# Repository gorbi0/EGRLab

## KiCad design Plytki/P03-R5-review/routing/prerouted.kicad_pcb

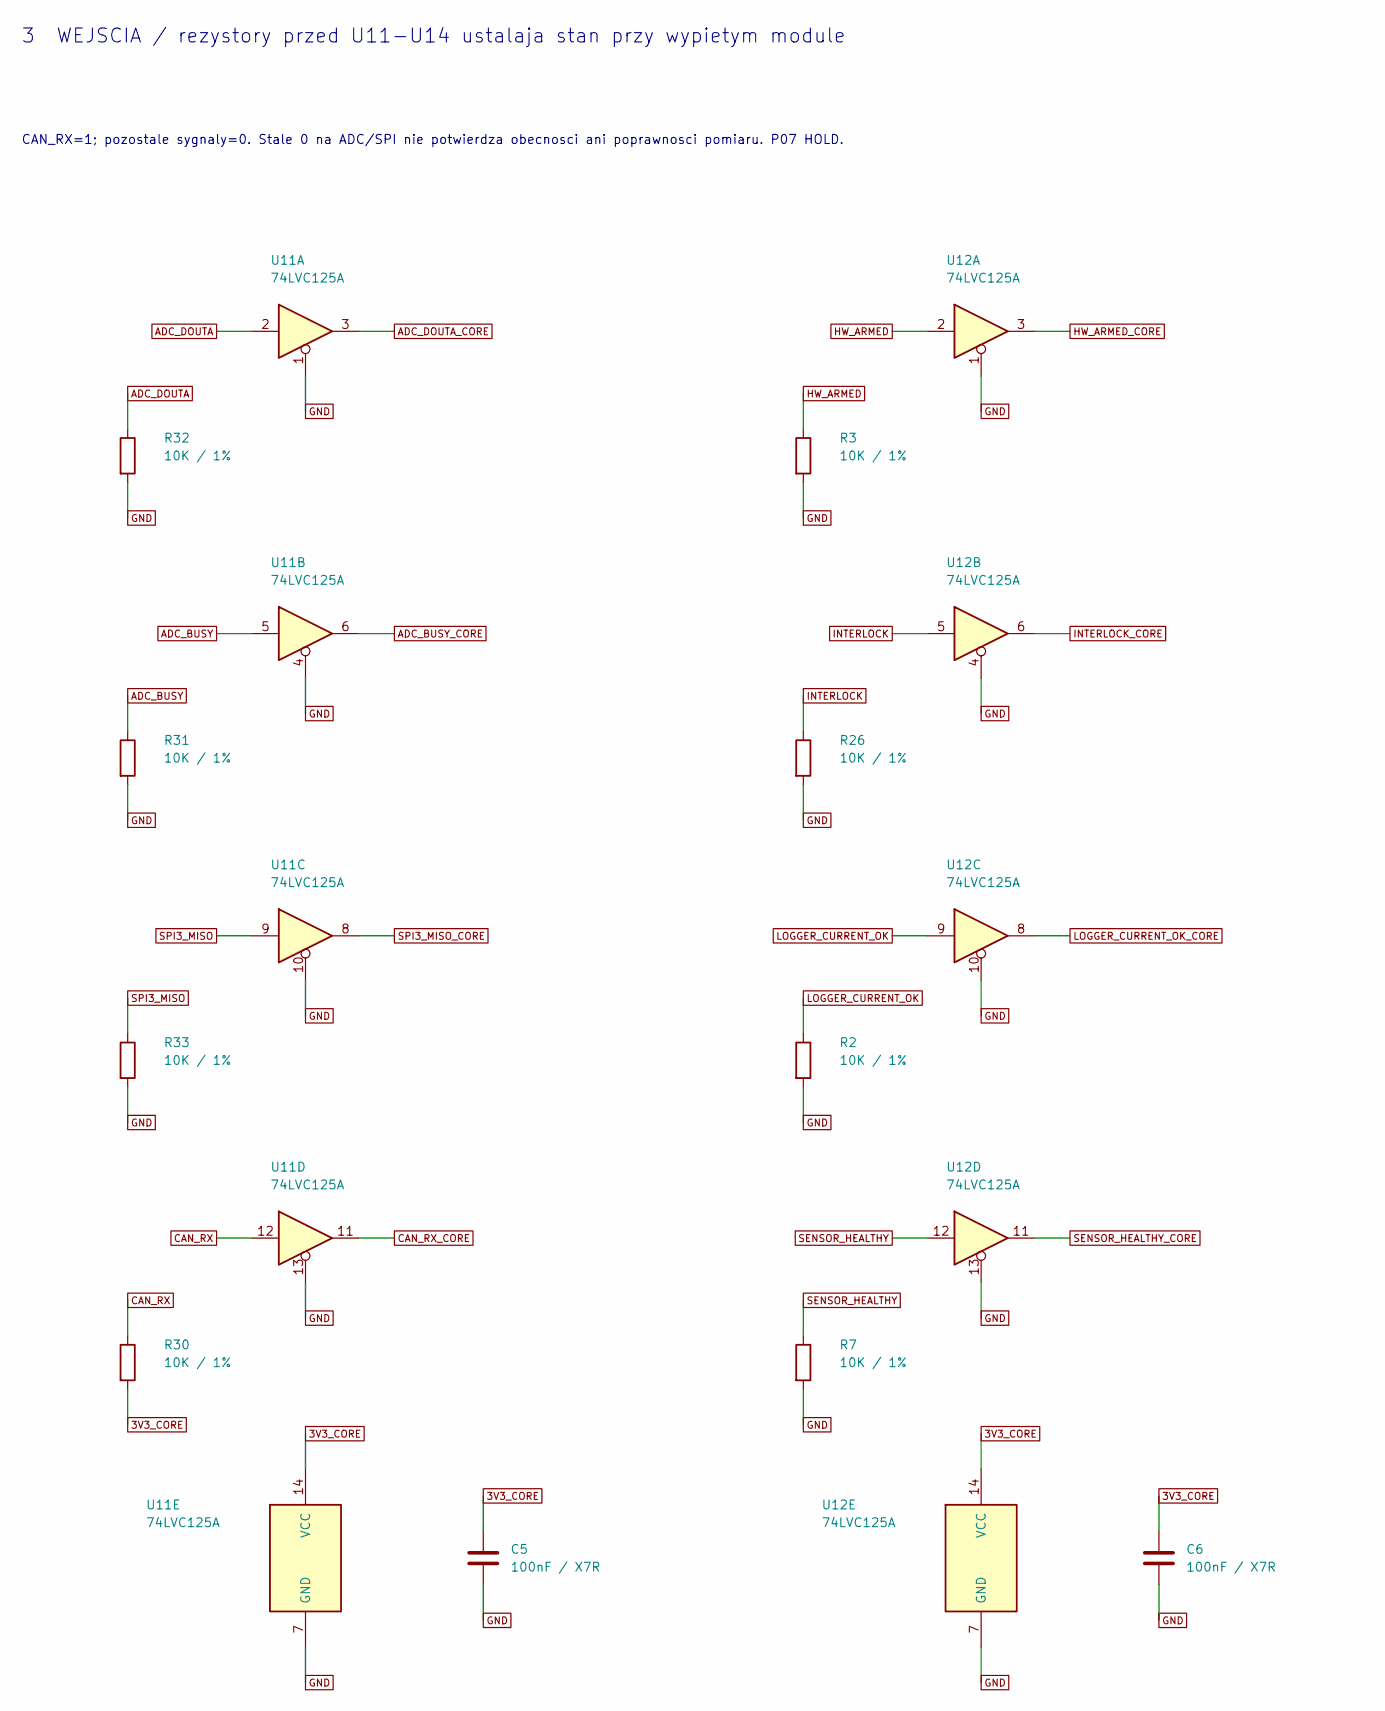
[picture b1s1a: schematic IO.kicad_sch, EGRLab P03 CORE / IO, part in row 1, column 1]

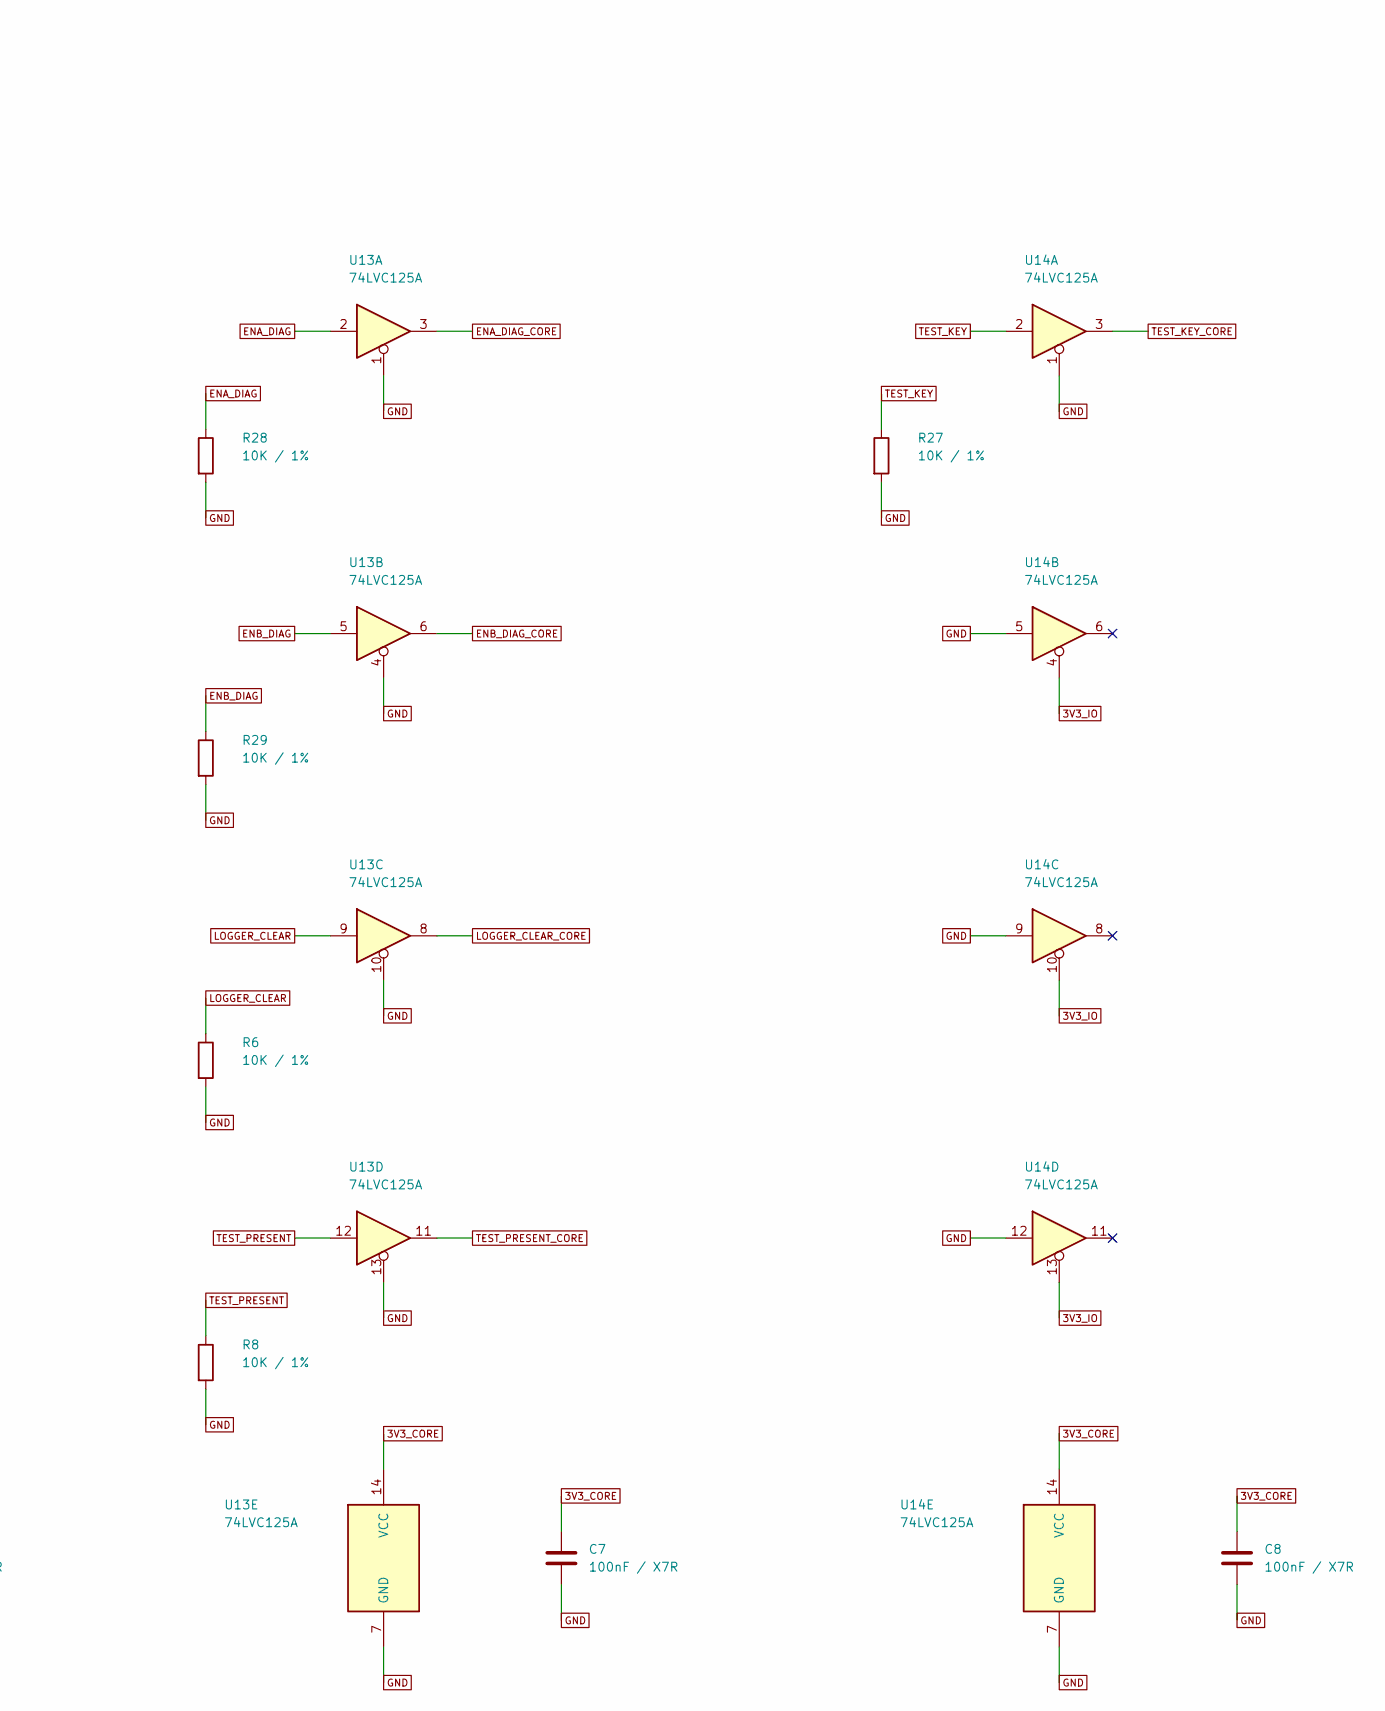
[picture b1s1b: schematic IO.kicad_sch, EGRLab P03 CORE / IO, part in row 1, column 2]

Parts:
C5, C6, C7, C8: 100nF / X7R; C_Vishay_K15_H5_P5; MPN K104K15X7RF53H5
R2, R3, R6, R7, R8, R26, R27, R28, R29, R30, R31, R32, R33: 10K / 1%; R_Axial_DIN0207_L6.3mm_D2.5mm_P10.16mm_Horizontal; MPN MF0207FTE-10K
U11, U12, U13, U14: 74LVC125A; Adapter_SO14_DIP14_W15.24_Kamami575068; MPN 74LVC125AD,118 (Nexperia) on Kamami 575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

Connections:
3V3_CORE: C5.1, C6.1, C7.1, C8.1, R30.2, U11.14 (VCC), U12.14 (VCC), U13.14 (VCC), U14.14 (VCC); also elsewhere on the board
3V3_IO: U14.4, U14.10, U14.13; also elsewhere on the board
ADC_BUSY: R31.1, U11.5; also elsewhere on the board
ADC_BUSY_CORE: U11.6; also elsewhere on the board
ADC_DOUTA: R32.1, U11.2; also elsewhere on the board
ADC_DOUTA_CORE: U11.3; also elsewhere on the board
CAN_RX: R30.1, U11.12; also elsewhere on the board
CAN_RX_CORE: U11.11; also elsewhere on the board
ENA_DIAG: R28.1, U13.2; also elsewhere on the board
ENA_DIAG_CORE: U13.3; also elsewhere on the board
ENB_DIAG: R29.1, U13.5; also elsewhere on the board
ENB_DIAG_CORE: U13.6; also elsewhere on the board
GND: C5.2, C6.2, C7.2, C8.2, R2.2, R3.2, R6.2, R7.2, R8.2, R26.2, R27.2, R28.2, R29.2, R31.2, R32.2, R33.2, U11.1, U11.4, U11.7 (GND), U11.10, U11.13, U12.1, U12.4, U12.7 (GND), U12.10, U12.13, U13.1, U13.4, U13.7 (GND), U13.10, U13.13, U14.1, U14.5, U14.7 (GND), U14.9, U14.12; also elsewhere on the board
HW_ARMED: R3.1, U12.2; also elsewhere on the board
HW_ARMED_CORE: U12.3; also elsewhere on the board
INTERLOCK: R26.1, U12.5; also elsewhere on the board
INTERLOCK_CORE: U12.6; also elsewhere on the board
LOGGER_CLEAR: R6.1, U13.9; also elsewhere on the board
LOGGER_CLEAR_CORE: U13.8; also elsewhere on the board
LOGGER_CURRENT_OK: R2.1, U12.9; also elsewhere on the board
LOGGER_CURRENT_OK_CORE: U12.8; also elsewhere on the board
SENSOR_HEALTHY: R7.1, U12.12; also elsewhere on the board
SENSOR_HEALTHY_CORE: U12.11; also elsewhere on the board
SPI3_MISO: R33.1, U11.9; also elsewhere on the board
SPI3_MISO_CORE: U11.8; also elsewhere on the board
TEST_KEY: R27.1, U14.2; also elsewhere on the board
TEST_KEY_CORE: U14.3; also elsewhere on the board
TEST_PRESENT: R8.1, U13.12; also elsewhere on the board
TEST_PRESENT_CORE: U13.11; also elsewhere on the board

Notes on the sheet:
3 WEJSCIA / rezystory przed U11-U14 ustalaja stan przy wypietym module
CAN_RX=1; pozostale sygnaly=0. Stale 0 na ADC/SPI nie potwierdza obecnosci ani poprawnosci pomiaru. P07 HOLD.

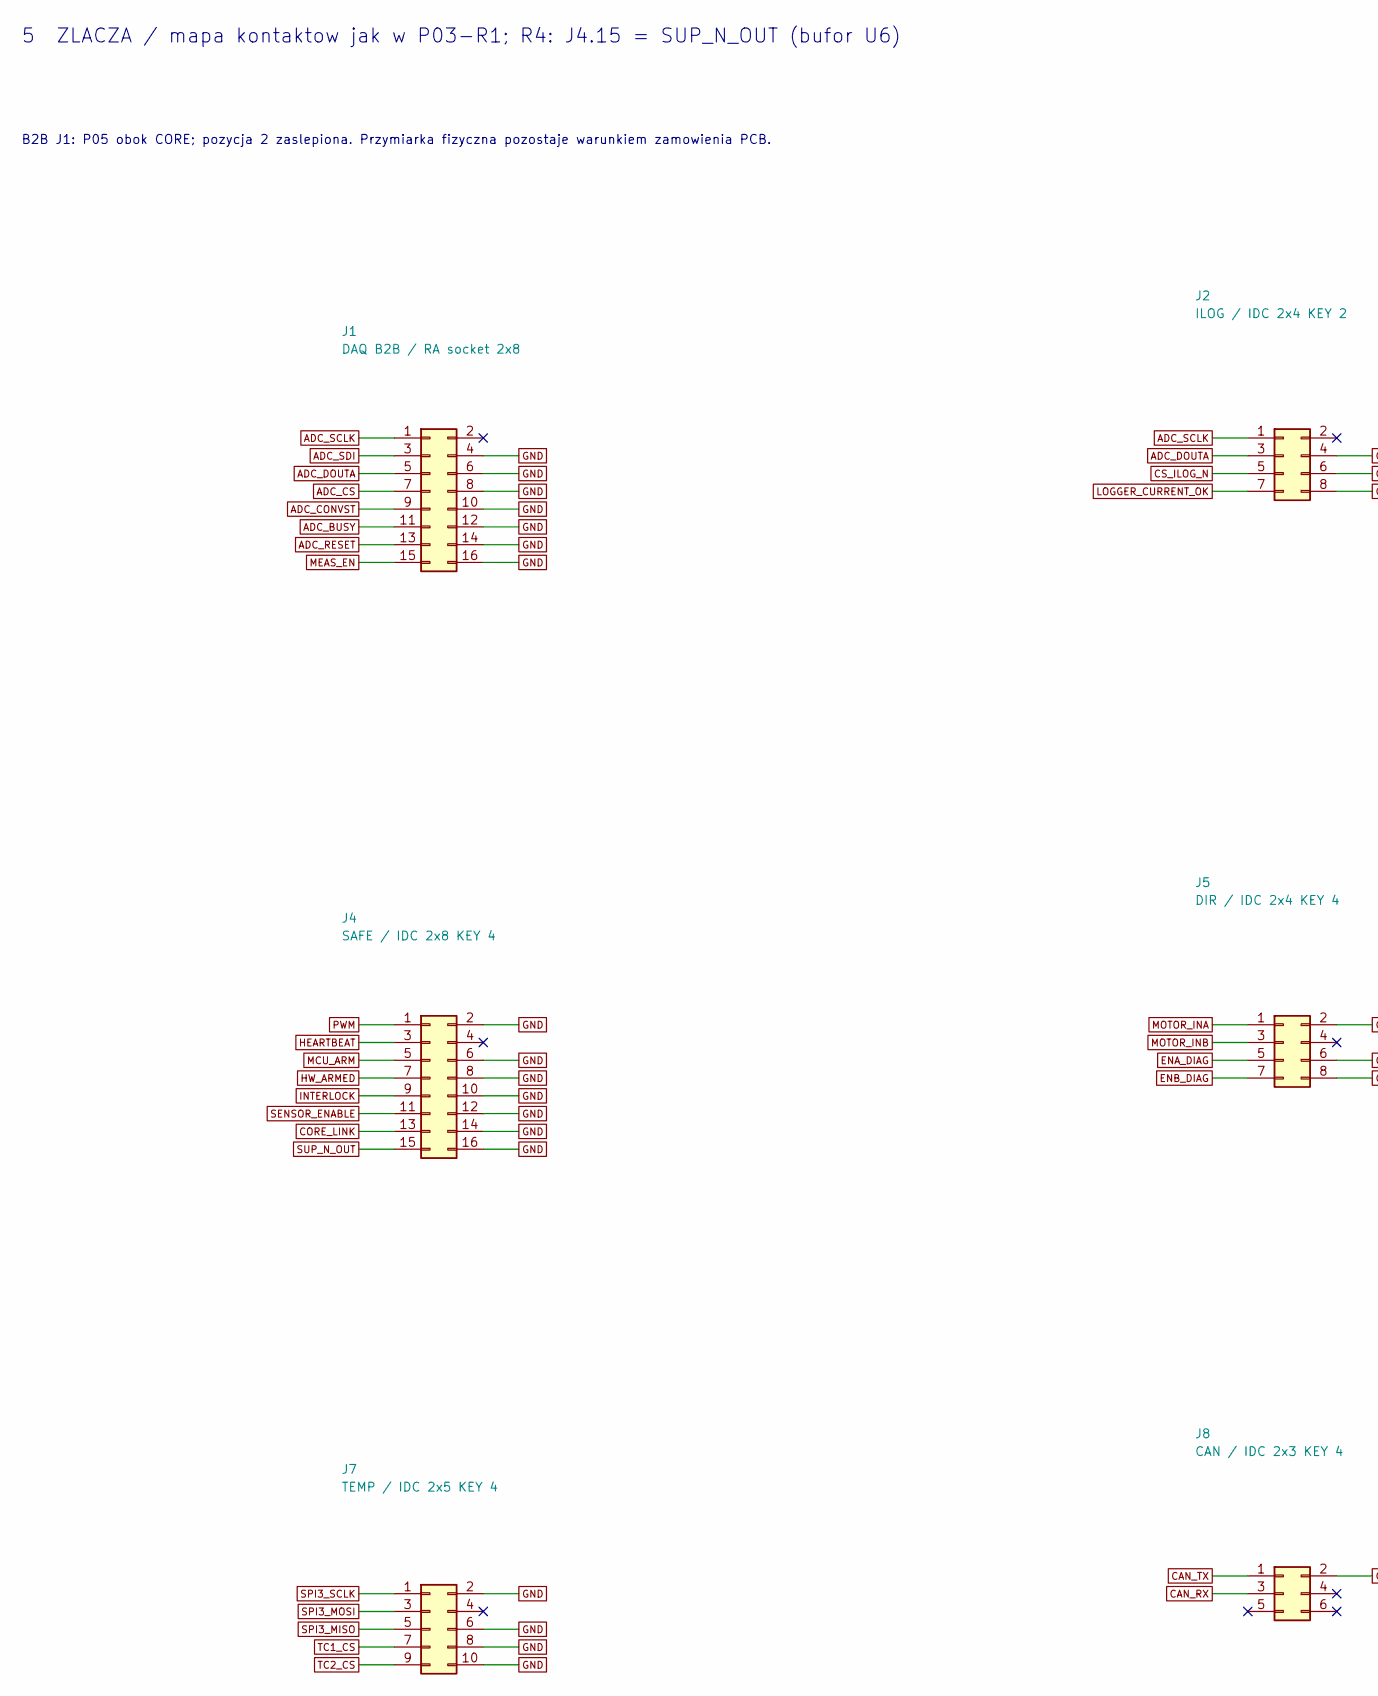
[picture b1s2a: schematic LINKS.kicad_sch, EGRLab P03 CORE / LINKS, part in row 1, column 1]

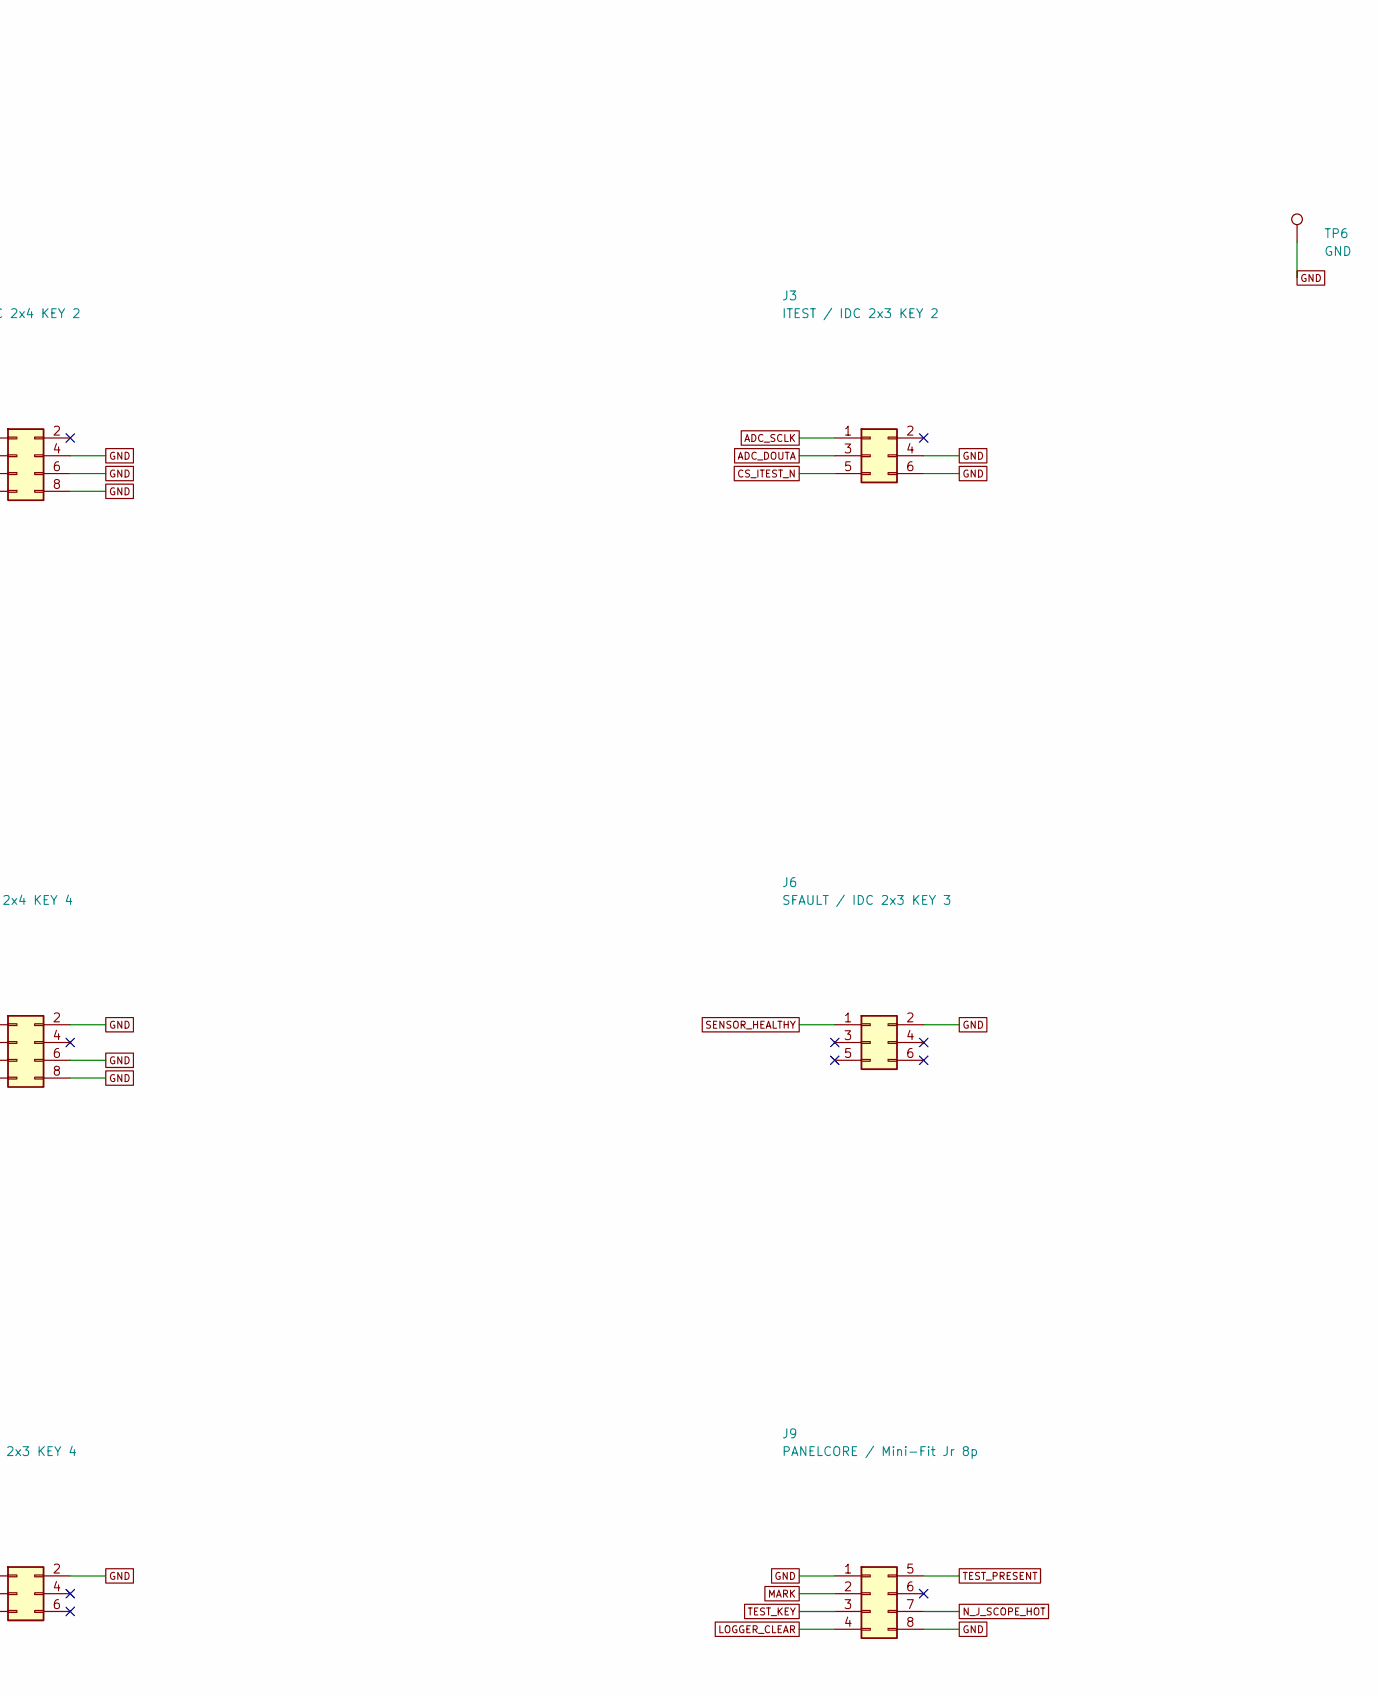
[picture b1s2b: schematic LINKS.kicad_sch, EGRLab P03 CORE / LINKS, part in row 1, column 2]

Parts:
J1: DAQ B2B / RA socket 2x8; PinSocket_2x08_P2.54mm_Horizontal; MPN Samtec SSW-108-02-G-D-RA (right-angle 2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
J2: ILOG / IDC 2x4 KEY 2; IDC-Header_2x04_P2.54mm_Vertical; MPN IDC box header 2x4, 2.54 mm, Au
J3: ITEST / IDC 2x3 KEY 2; IDC-Header_2x03_P2.54mm_Vertical; MPN IDC box header 2x3, 2.54 mm, Au
J4: SAFE / IDC 2x8 KEY 4; IDC-Header_2x08_P2.54mm_Vertical; MPN IDC box header 2x8, 2.54 mm, Au
J5: DIR / IDC 2x4 KEY 4; IDC-Header_2x04_P2.54mm_Vertical; MPN IDC box header 2x4, 2.54 mm, Au
J6: SFAULT / IDC 2x3 KEY 3; IDC-Header_2x03_P2.54mm_Vertical; MPN IDC box header 2x3, 2.54 mm, Au
J7: TEMP / IDC 2x5 KEY 4; IDC-Header_2x05_P2.54mm_Vertical; MPN IDC box header 2x5, 2.54 mm, Au
J8: CAN / IDC 2x3 KEY 4; IDC-Header_2x03_P2.54mm_Vertical; MPN IDC box header 2x3, 2.54 mm, Au
J9: PANELCORE / Mini-Fit Jr 8p; Molex_Mini-Fit_Jr_5566-08A_2x04_P4.20mm_Vertical; MPN Molex Mini-Fit Jr 5566-08A vertical, Au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
TP6: GND; TestPad_1; MPN PCB test pad

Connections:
ADC_BUSY: J1.11; also elsewhere on the board
ADC_CONVST: J1.9; also elsewhere on the board
ADC_CS: J1.7; also elsewhere on the board
ADC_DOUTA: J1.5, J2.3, J3.3; also elsewhere on the board
ADC_RESET: J1.13; also elsewhere on the board
ADC_SCLK: J1.1, J2.1, J3.1; also elsewhere on the board
ADC_SDI: J1.3; also elsewhere on the board
CAN_RX: J8.3; also elsewhere on the board
CAN_TX: J8.1; also elsewhere on the board
CORE_LINK: J4.13; also elsewhere on the board
CS_ILOG_N: J2.5; also elsewhere on the board
CS_ITEST_N: J3.5; also elsewhere on the board
ENA_DIAG: J5.5; also elsewhere on the board
ENB_DIAG: J5.7; also elsewhere on the board
GND: J1.4, J1.6, J1.8, J1.10, J1.12, J1.14, J1.16, J2.4, J2.6, J2.8, J3.4, J3.6, J4.2, J4.6, J4.8, J4.10, J4.12, J4.14, J4.16, J5.2, J5.6, J5.8, J6.2, J7.2, J7.6, J7.8, J7.10, J8.2, J9.1, J9.8, TP6.1; also elsewhere on the board
HEARTBEAT: J4.3; also elsewhere on the board
HW_ARMED: J4.7; also elsewhere on the board
INTERLOCK: J4.9; also elsewhere on the board
LOGGER_CLEAR: J9.4; also elsewhere on the board
LOGGER_CURRENT_OK: J2.7; also elsewhere on the board
MARK: J9.2; also elsewhere on the board
MCU_ARM: J4.5; also elsewhere on the board
MEAS_EN: J1.15; also elsewhere on the board
MOTOR_INA: J5.1; also elsewhere on the board
MOTOR_INB: J5.3; also elsewhere on the board
N_J_SCOPE_HOT: J9.7; also elsewhere on the board
PWM: J4.1; also elsewhere on the board
SENSOR_ENABLE: J4.11; also elsewhere on the board
SENSOR_HEALTHY: J6.1; also elsewhere on the board
SPI3_MISO: J7.5; also elsewhere on the board
SPI3_MOSI: J7.3; also elsewhere on the board
SPI3_SCLK: J7.1; also elsewhere on the board
SUP_N_OUT: J4.15; also elsewhere on the board
TC1_CS: J7.7; also elsewhere on the board
TC2_CS: J7.9; also elsewhere on the board
TEST_KEY: J9.3; also elsewhere on the board
TEST_PRESENT: J9.5; also elsewhere on the board

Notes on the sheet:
5 ZLACZA / mapa kontaktow jak w P03-R1; R4: J4.15 = SUP_N_OUT (bufor U6)
B2B J1: P05 obok CORE; pozycja 2 zaslepiona. Przymiarka fizyczna pozostaje warunkiem zamowienia PCB.

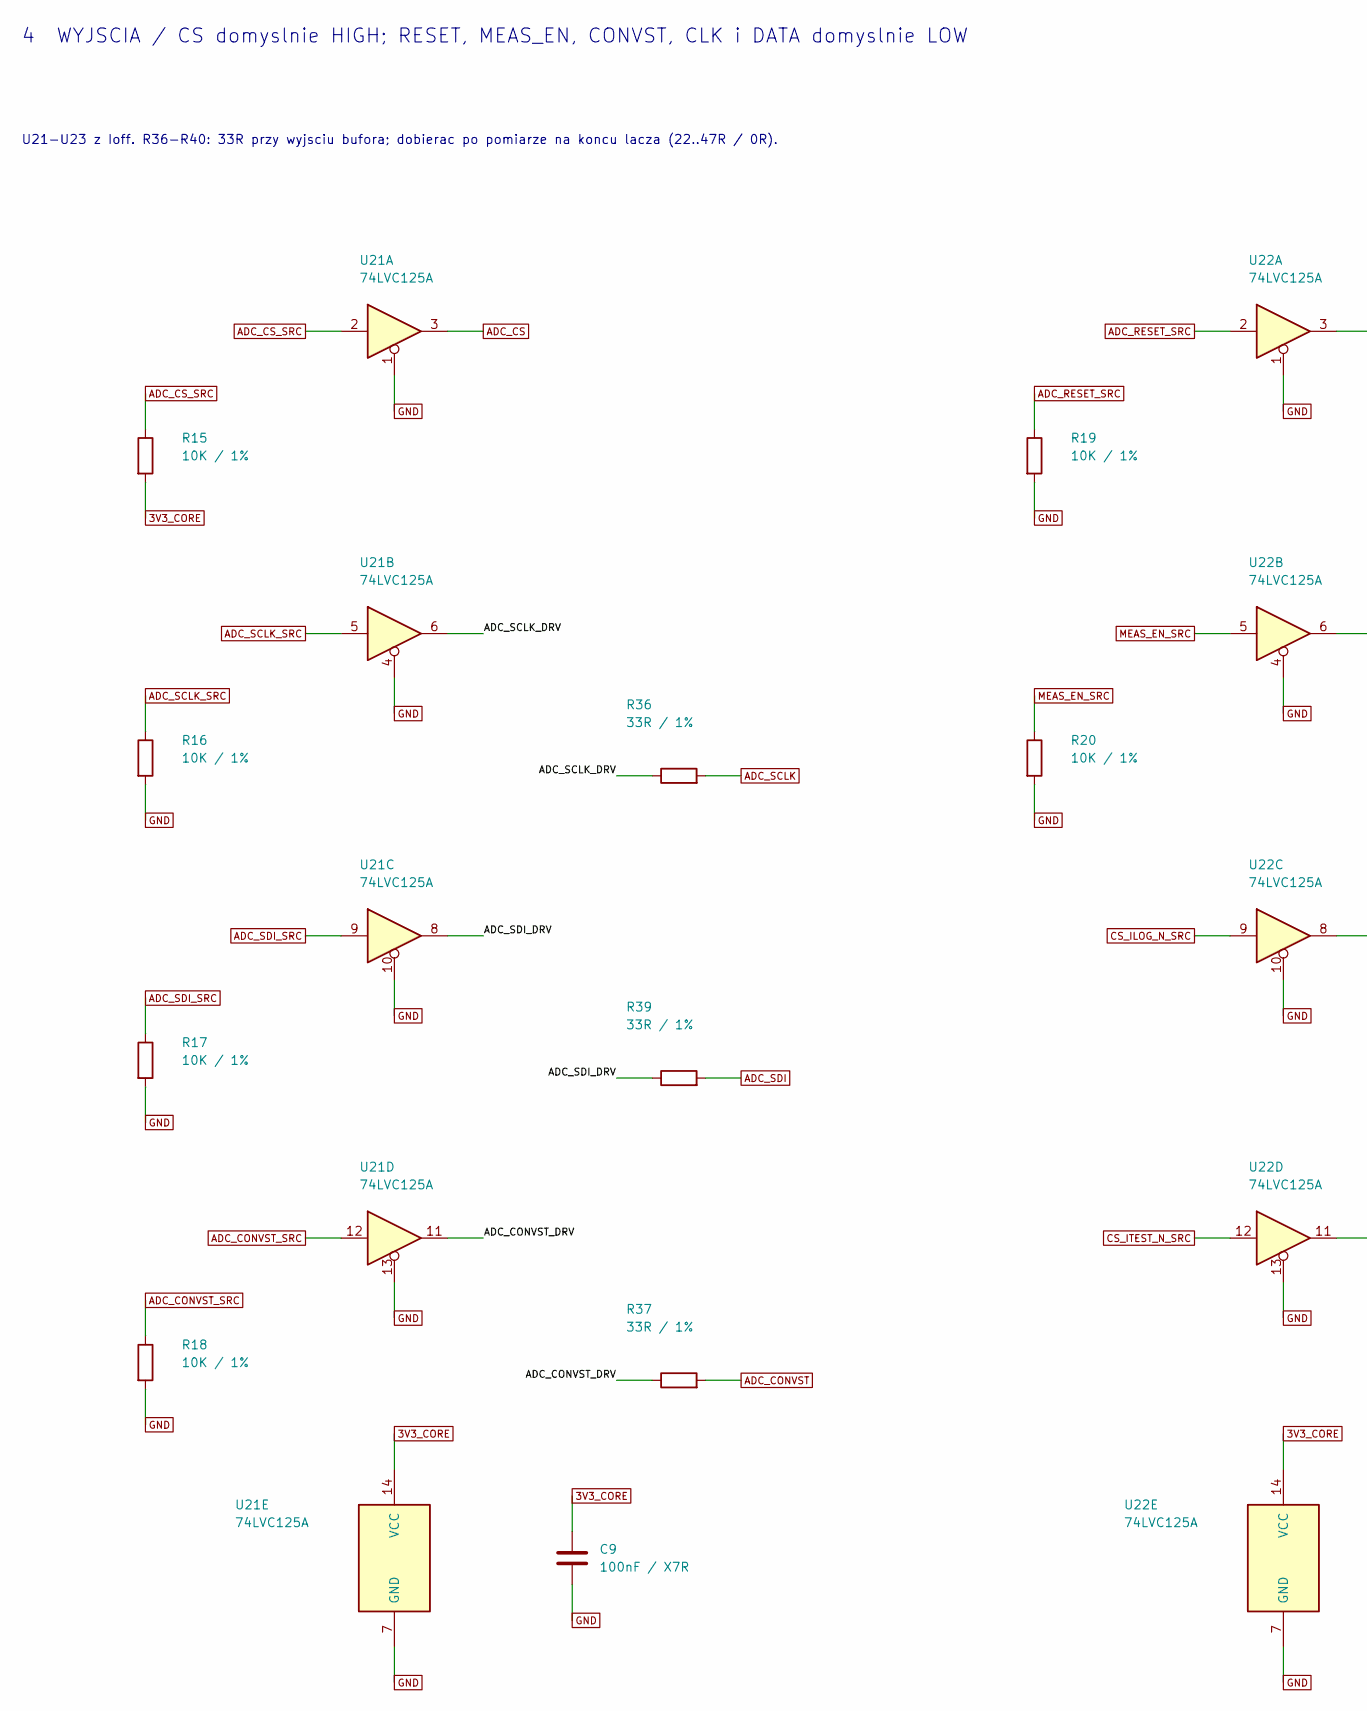
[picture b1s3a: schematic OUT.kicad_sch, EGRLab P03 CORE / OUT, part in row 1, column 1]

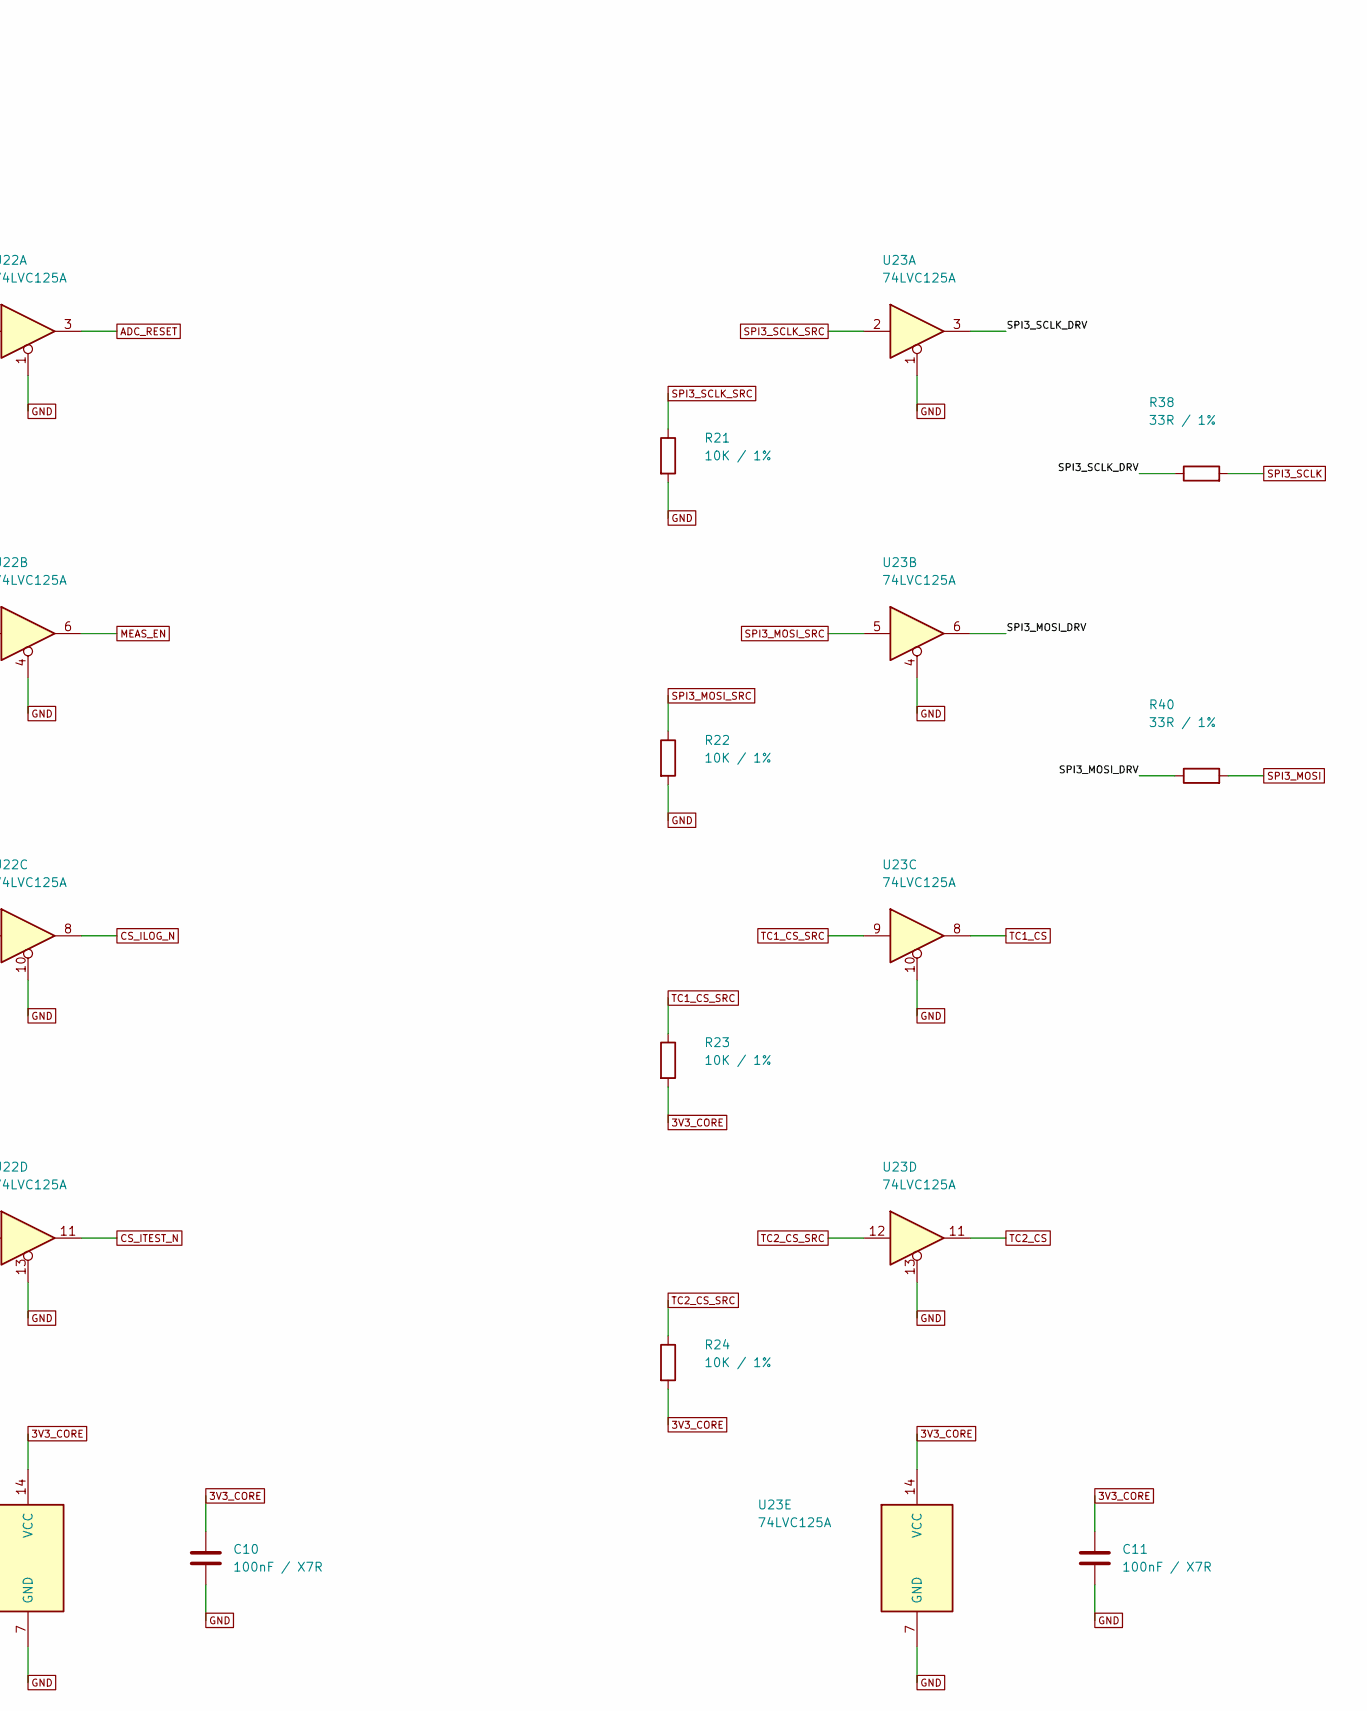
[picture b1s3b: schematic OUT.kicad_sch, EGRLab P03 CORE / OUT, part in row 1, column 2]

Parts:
C9, C10, C11: 100nF / X7R; C_Vishay_K15_H5_P5; MPN K104K15X7RF53H5
R15, R16, R17, R18, R19, R20, R21, R22, R23, R24: 10K / 1%; R_Axial_DIN0207_L6.3mm_D2.5mm_P10.16mm_Horizontal; MPN MF0207FTE-10K
R36, R37, R38, R39, R40: 33R / 1%; R_Axial_DIN0207_L6.3mm_D2.5mm_P10.16mm_Horizontal; MPN MF0207FTE-33R
U21, U22, U23: 74LVC125A; Adapter_SO14_DIP14_W15.24_Kamami575068; MPN 74LVC125AD,118 (Nexperia) on Kamami 575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

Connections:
3V3_CORE: C9.1, C10.1, C11.1, R15.2, R23.2, R24.2, U21.14 (VCC), U22.14 (VCC), U23.14 (VCC); also elsewhere on the board
/OUT/ADC_CONVST_DRV: R37.1, U21.11
/OUT/ADC_SCLK_DRV: R36.1, U21.6
/OUT/ADC_SDI_DRV: R39.1, U21.8
/OUT/SPI3_MOSI_DRV: R40.1, U23.6
/OUT/SPI3_SCLK_DRV: R38.1, U23.3
ADC_CONVST: R37.2; also elsewhere on the board
ADC_CONVST_SRC: R18.1, U21.12; also elsewhere on the board
ADC_CS: U21.3; also elsewhere on the board
ADC_CS_SRC: R15.1, U21.2; also elsewhere on the board
ADC_RESET: U22.3; also elsewhere on the board
ADC_RESET_SRC: R19.1, U22.2; also elsewhere on the board
ADC_SCLK: R36.2; also elsewhere on the board
ADC_SCLK_SRC: R16.1, U21.5; also elsewhere on the board
ADC_SDI: R39.2; also elsewhere on the board
ADC_SDI_SRC: R17.1, U21.9; also elsewhere on the board
CS_ILOG_N: U22.8; also elsewhere on the board
CS_ILOG_N_SRC: U22.9; also elsewhere on the board
CS_ITEST_N: U22.11; also elsewhere on the board
CS_ITEST_N_SRC: U22.12; also elsewhere on the board
GND: C9.2, C10.2, C11.2, R16.2, R17.2, R18.2, R19.2, R20.2, R21.2, R22.2, U21.1, U21.4, U21.7 (GND), U21.10, U21.13, U22.1, U22.4, U22.7 (GND), U22.10, U22.13, U23.1, U23.4, U23.7 (GND), U23.10, U23.13; also elsewhere on the board
MEAS_EN: U22.6; also elsewhere on the board
MEAS_EN_SRC: R20.1, U22.5; also elsewhere on the board
SPI3_MOSI: R40.2; also elsewhere on the board
SPI3_MOSI_SRC: R22.1, U23.5; also elsewhere on the board
SPI3_SCLK: R38.2; also elsewhere on the board
SPI3_SCLK_SRC: R21.1, U23.2; also elsewhere on the board
TC1_CS: U23.8; also elsewhere on the board
TC1_CS_SRC: R23.1, U23.9; also elsewhere on the board
TC2_CS: U23.11; also elsewhere on the board
TC2_CS_SRC: R24.1, U23.12; also elsewhere on the board

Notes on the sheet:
4 WYJSCIA / CS domyslnie HIGH; RESET, MEAS_EN, CONVST, CLK i DATA domyslnie LOW
U21-U23 z Ioff. R36-R40: 33R przy wyjsciu bufora; dobierac po pomiarze na koncu lacza (22..47R / 0R).
